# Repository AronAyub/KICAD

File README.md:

# KICAD
- **Some Old designs, this is where i began ! **
- kicad design projects
  
In this repository I have provided my previous KICAD PCB Designs for:
### Arduino hat
- this is a complete arduino hat, check the folder for files! it is among my first designs 

### Breadboard - Power Supply
- most devs use breadborad for their prototyping, learn how to create a breadboard power supply. it is among my first designs 

### Flamingo Control Board
- this was a client project, he allowed to have it open source. He is from Florida! funny enough he wanted a Flamingo shapped PCB, it is among my first designs 

### 12V 1A input to 3v3 /5V circuit 

- this is a simple power supply unit which accepts 12V, 1A and gives, 3V3 and 5V as output, it is among my first designs 

### LED Matrix Project
 - An LED Matrix based PCB using registers, this was implimented practically locally in Kenya.

### Raspberry pi Hat project

- mini Pi Hat, one of my old PCB design projects !

### Rf 2.45ghz support circuit
- the circuit schematic is in the folder 

### STRF-Kicad master
- the circuit schematic is in the folder
### 3-phase circuit
- the circuit schematic is in the folder
### Transmitter Circuit 
- the circuit schematic is in the folder

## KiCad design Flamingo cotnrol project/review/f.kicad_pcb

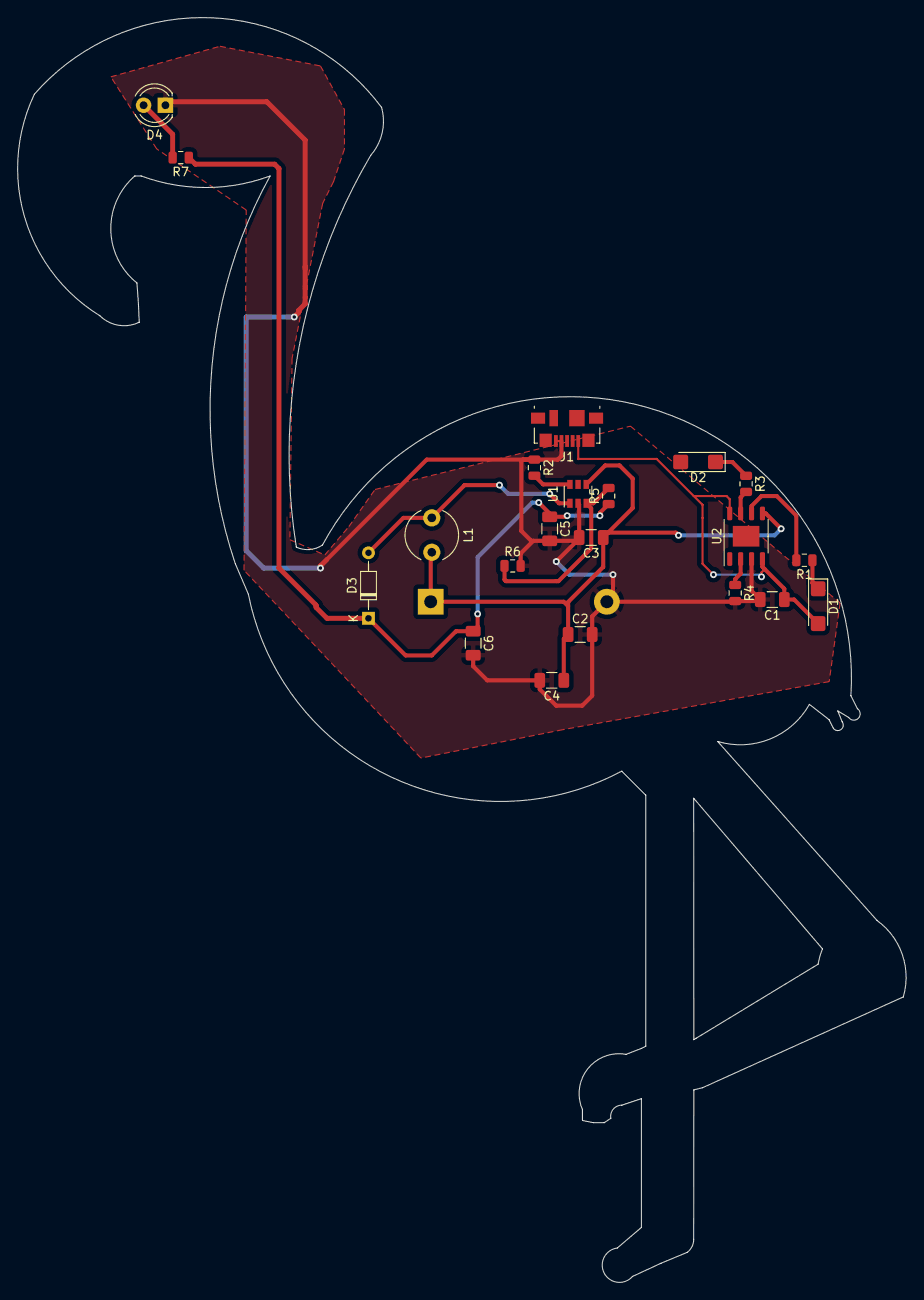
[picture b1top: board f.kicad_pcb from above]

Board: 2 copper layers, 103.4 x 147.1 mm, 22 parts (1 on the bottom side), 13 nets.

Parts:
BT1: Battery; BatteryHolder_Keystone_104_1x23mm
C1, C4: 10nF; C_1206_3216Metric
C2, C5: 20uF; C_1206_3216Metric
C3, C6: 0.1uF; C_1206_3216Metric
D1: GREEN; LED_1806_4516Metric_Castellated
D2: RED; LED_1806_4516Metric_Castellated
D3: 5.1; D_DO-34_SOD68_P7.62mm_Horizontal
D4: LED; LED_D4.0mm
J1: USB_A; USB_Micro-B_Molex_47346-0001
L1: 4.7uH; L_Radial_D6.0mm_P4.00mm
R1, R3, R7: 1k; R_0805_2012Metric
R2: 48k; R_0805_2012Metric
R4: 1.2k; R_0805_2012Metric
R5: 88k; R_0805_2012Metric
R6: 12k; R_0805_2012Metric
U1: FP6291; SOT-23-6
U2: TP4056_BT; HSOP-8-1EP_3.9x4.9mm_P1.27mm_EP2.41x3.1mm

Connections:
5OT: C5.1, C6.1, D3.1 (K), R5.1, R7.1
BAT-: BT1.2 (-), C1.2, C2.2, C3.2, C4.2, C5.2, C6.2, D4.1 (K), J1.4 (GND), J1.5 (Shield), R2.1, R4.2, R6.2, U1.2 (GND), U2.3 (GND_)
BOOST: BT1.1 (+), C2.1, C3.1, C4.1, L1.2, U1.4 (EN), U1.5 (VCC), U2.5 (BAT)
FB: R5.2, R6.1, U1.3 (FB)
unnamed: C1.1, D1.2 (A), D2.2 (A), J1.1 (VBUS), U2.4 (VCC), U2.8 (CE)
unnamed: D1.1 (K), R1.1
unnamed: D2.1 (K), R3.1
unnamed: D3.2 (A), L1.1, U1.1 (LX)
unnamed: D4.2 (A), R7.2
unnamed: R1.2, U2.6 (STDBY)
unnamed: R2.2, U1.6 (OC)
unnamed: R3.2, U2.7 (CHRG)
unnamed: R4.1, U2.2 (PROG)

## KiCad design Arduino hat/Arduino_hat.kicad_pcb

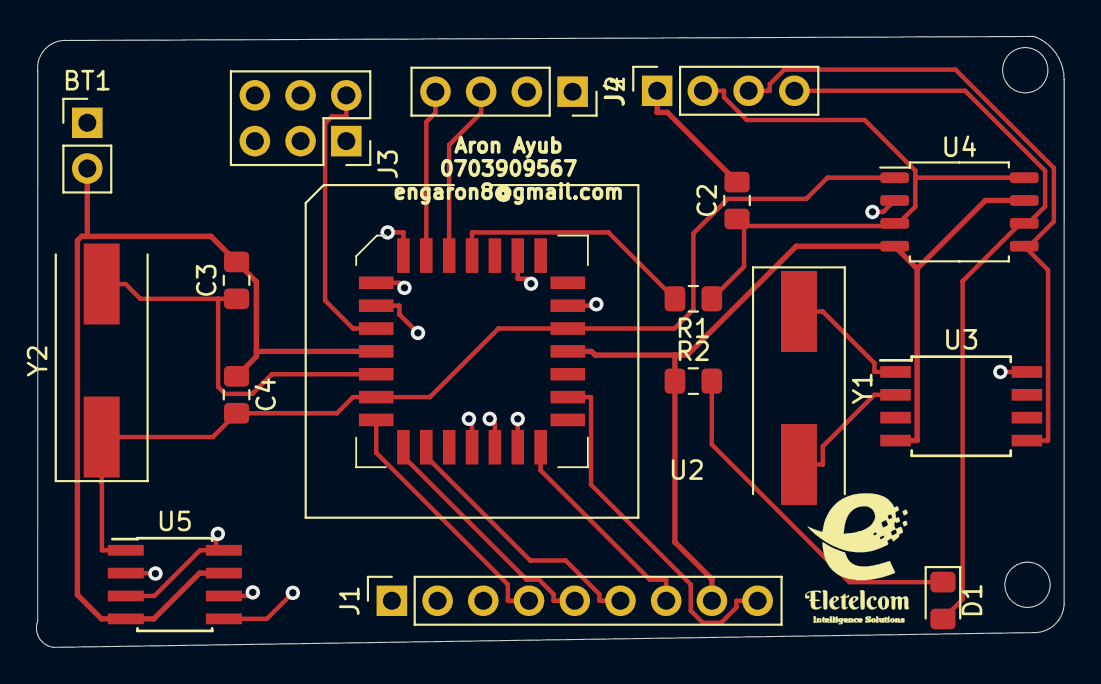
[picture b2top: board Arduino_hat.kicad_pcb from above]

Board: 4 copper layers, 57.1 x 33.9 mm, 17 parts (0 on the bottom side), 22 nets.

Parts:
BT1: 3V; PinHeader_1x02_P2.54mm_Vertical
C2: 10uF; C_0805_2012Metric_Pad1.15x1.40mm_HandSolder
C3, C4: 22pF; C_0805_2012Metric_Pad1.15x1.40mm_HandSolder
D1: LED; LED_0805_2012Metric_Pad1.15x1.40mm_HandSolder
J1: digital pins; PinSocket_1x09_P2.54mm_Vertical
J2: I2C; PinSocket_1x04_P2.54mm_Vertical
J3: ICSP; PinSocket_2x03_P2.54mm_Vertical
J4: serial; PinSocket_1x04_P2.54mm_Vertical
R1: 10Kohm; R_0805_2012Metric_Pad1.15x1.40mm_HandSolder
R2: 330ohm; R_0805_2012Metric_Pad1.15x1.40mm_HandSolder
U2: ATmega328P-PU; PLCC-28_SMD-Socket
U3: DS1337_PDv2; SOIJ-8_5.3x5.3mm_P1.27mm
U4: 24LC1025; SOIC-8_5.275x5.275mm_P1.27mm
U5: 24LC1025; PowerIntegrations_SO-8
Y1: Crystal 32MHz; Crystal_SMD_HC49-SD
Y2: Crystal 16Mhz; Crystal_SMD_HC49-SD

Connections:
/ADDR1: C4.2, U2.10, U2.23, U4.1, U5.1, Y2.1
/ADDR2: U2.24, U4.2, U5.2
/D2: J1.1, U2.4
/D3: J1.2, U2.5
/D4: J1.3, U2.6
/D5: J1.4, U2.11
/D6: J1.5, U2.12
/D7: J1.6, U2.13
/D8: J1.7, U2.18
/MISO: J3.1, U2.16
/MOSI: J3.4, U2.15
/RESET: R1.2, U2.1
/RX: J4.3, U2.2
/SCK: D1.2, J2.4, J3.3, U2.17, U4.6, U5.6
/SDA: J2.3, U2.27, U3.5, U4.5, U5.5
/TX: J4.4, U2.3
/VCC: BT1.1, C2.1, J1.9, J2.2, J3.2, J4.2, R1.1, U2.7, U2.20, U3.8, U4.3, U4.8, U5.3, U5.8
GNDPWR: BT1.2, C2.2, C3.2, C4.1, J1.8, J2.1, J3.6, J4.1, R2.1, U2.8, U2.22, U3.4, U4.4, U4.7, U5.4, U5.7
unnamed: C3.1, U2.9, Y2.2
unnamed: D1.1, R2.2
unnamed: U3.1, Y1.1
unnamed: U3.2, Y1.2

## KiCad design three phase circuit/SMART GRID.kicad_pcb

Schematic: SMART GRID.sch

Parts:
1Mohm1, 1Mohm2, 1Mohm3, 1Mohm4, 1Mohm5: 47k; R_Axial_DIN0309_L9.0mm_D3.2mm_P12.70mm_Horizontal
C1, C2, C6, C7, C8, C9: 2A103J; C_Disc_D9.0mm_W5.0mm_P5.00mm
C3, C10, C11: 10uF 16v; CP_Radial_D4.0mm_P1.50mm
C4, C12, C13: 47uf; CP_Radial_D4.0mm_P1.50mm
C5: 2A104J; C_Disc_D9.0mm_W5.0mm_P5.00mm
C14, C15: 2A104J; C_Disc_D11.0mm_W5.0mm_P5.00mm
C16: 2A123J; C_Disc_D11.0mm_W5.0mm_P5.00mm
C17: 2A123J; C_Disc_D11.0mm_W5.0mm_P7.50mm
C18: 2A104J; C_Disc_D11.0mm_W5.0mm_P7.50mm
D1: 1N4007-T_NRND; DO-41; MPN 1N4007-T; Digi-Key_PN 1N4007DICT-ND
D2, D3, D4, D5, D6, D7, D8, D9, D10, D11, D12: 1N4007-T_NRND; D_5W_P12.70mm_Horizontal; MPN 1N4007-T; Digi-Key_PN 1N4007DICT-ND
J1: Screw_Terminal_01x04; TerminalBlock_Altech_AK300-4_P5.00mm
R1: 1M; R_Axial_DIN0309_L9.0mm_D3.2mm_P12.70mm_Horizontal
R2, R7, R11: 100K; R_Axial_DIN0309_L9.0mm_D3.2mm_P15.24mm_Horizontal
R3, R5, R8, R12, R14, R15: 10K; R_Axial_DIN0309_L9.0mm_D3.2mm_P15.24mm_Horizontal
R4, R9, R13: 2.2K; R_Axial_DIN0309_L9.0mm_D3.2mm_P15.24mm_Horizontal
R6, R10: 1M; R_Axial_DIN0309_L9.0mm_D3.2mm_P15.24mm_Horizontal
R16: 47k; R_Axial_DIN0309_L9.0mm_D3.2mm_P15.24mm_Horizontal
U1, U2, U3: LM3578; DIP-8_W7.62mm

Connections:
/A0: R16.1, U1.1
/A1: 1Mohm1.1, U2.1
/A2: 1Mohm3.1, U3.1
/GND: 1Mohm2.2, 1Mohm4.2, 1Mohm5.2, C1.2, C2.2, C3.2, C4.2, C5.1, C6.2, C7.2, C8.2, C9.2, C10.2, C11.2, C12.2, C13.2, C14.1, C15.1, C16.1, C17.1, C18.1, R4.2, R9.2, R13.2, U1.4, U2.4, U3.4; also elsewhere on the board
/L1: D1.K, J1.4
/L2: J1.3
/L3: J1.2
/N: D1.A, J1.1
/SG1: C1.1, R1.1
/SG2: C6.1, R6.1
/SG3: C7.1, R10.1
/VCC: C16.2, C17.2, C18.2, U1.8, U2.8, U3.8; also elsewhere on the board
unnamed: 1Mohm1.2, 1Mohm4.1, U2.2
unnamed: 1Mohm2.1, R16.2, U1.2
unnamed: 1Mohm3.2, 1Mohm5.1, U3.2
unnamed: C2.1, C3.1, R3.2, R4.1, R5.2
unnamed: C4.1, R5.1
unnamed: C5.2, U1.5
unnamed: C8.1, C10.1, R8.2, R9.1, R14.2
unnamed: C9.1, C11.1, R12.2, R13.1, R15.2
unnamed: C12.1, R14.1
unnamed: C13.1, R15.1
unnamed: C14.2, U2.5
unnamed: C15.2, U3.5
unnamed: R1.2, R2.1
unnamed: R2.2, R3.1
unnamed: R6.2, R7.1
unnamed: R7.2, R8.1
unnamed: R10.2, R11.1
unnamed: R11.2, R12.1
unnamed: U1.3, U1.6, U1.7
unnamed: U2.3, U2.6, U2.7
unnamed: U3.3, U3.6, U3.7

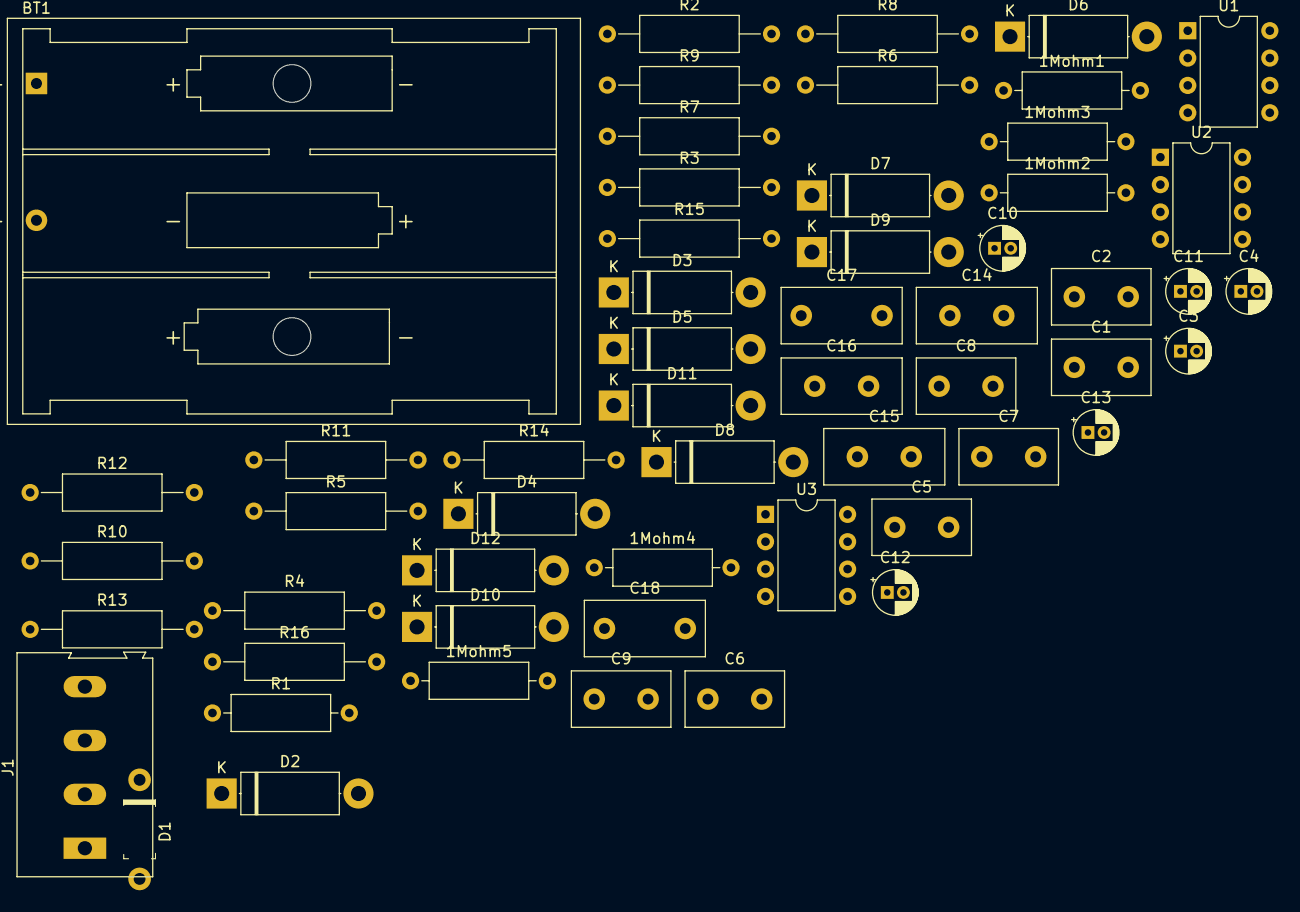
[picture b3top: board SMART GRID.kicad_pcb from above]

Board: 2 copper layers, 56 parts (0 on the bottom side), 31 nets, no tracks yet.

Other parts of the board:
BT1: 6V; BatteryHolder_Keystone_2479_3xAAA

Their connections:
/GND: BT1.2; also elsewhere on the board
/VCC: BT1.1; also elsewhere on the board

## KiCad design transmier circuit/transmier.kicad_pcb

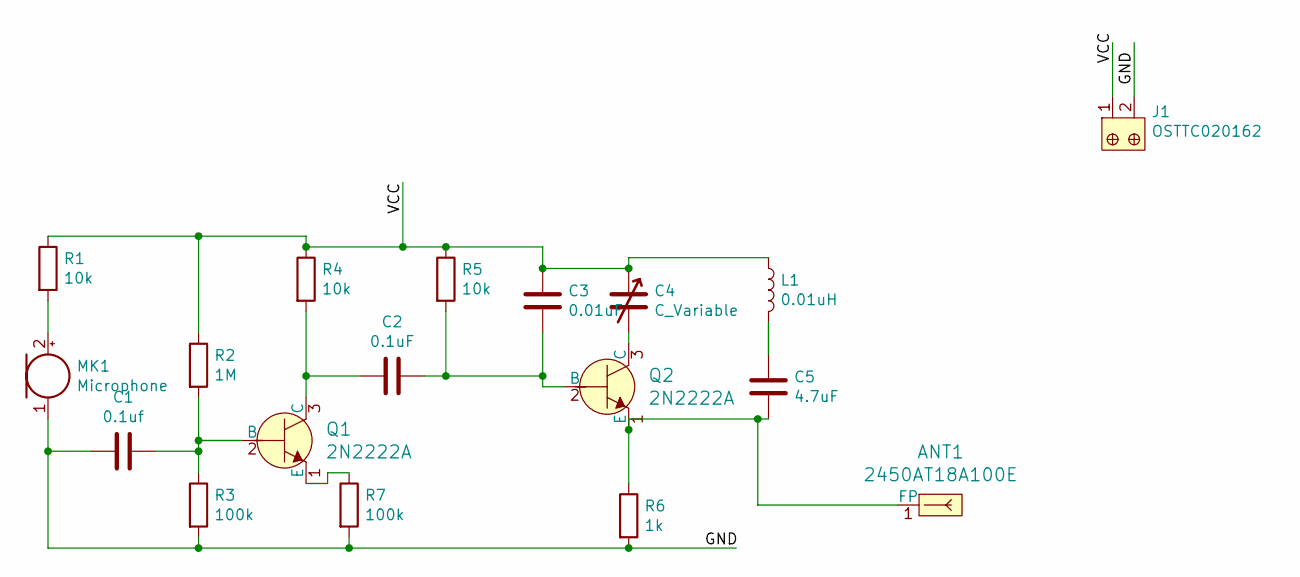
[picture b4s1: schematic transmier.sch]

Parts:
ANT1: 2450AT18A100E; Pin_D0.9mm_L10.0mm_W2.4mm_FlatFork; MPN 2450AT18A100E; Digi-Key_PN 712-1005-1-ND
C1: 0.1uf; C_Disc_D12.0mm_W4.4mm_P7.75mm
C2: 0.1uF; C_Disc_D12.0mm_W4.4mm_P7.75mm
C3: 0.01uF; C_Disc_D12.0mm_W4.4mm_P7.75mm
C4: C_Variable; C_Rect_L7.0mm_W6.5mm_P5.00mm
C5: 4.7uF; C_Disc_D7.5mm_W5.0mm_P5.00mm
J1: OSTTC020162; C_Disc_D12.0mm_W4.4mm_P7.75mm; MPN OSTTC020162; Digi-Key_PN ED2600-ND
L1: 0.01uH; L_Axial_L14.0mm_D4.5mm_P15.24mm_Horizontal_Fastron_LACC
MK1: Microphone; L_Radial_D10.5mm_P5.00mm_Abacron_AISR-01
Q1, Q2: 2N2222A; TO-18-3; MPN 2N2222A; Digi-Key_PN 2N2222ACS-ND
R1, R4, R5: 10k; R_Axial_DIN0614_L14.3mm_D5.7mm_P15.24mm_Horizontal
R2: 1M; R_Axial_DIN0614_L14.3mm_D5.7mm_P15.24mm_Horizontal
R3, R7: 100k; R_Axial_DIN0614_L14.3mm_D5.7mm_P15.24mm_Horizontal
R6: 1k; R_Axial_DIN0614_L14.3mm_D5.7mm_P15.24mm_Horizontal

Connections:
/GND: C1.2, J1.2, MK1.1 (-), R3.2, R6.2, R7.2
/VCC: C3.2, C4.1, J1.1, L1.1, R1.1, R2.1, R4.1, R5.1
unnamed: ANT1.1 (FP), C5.1, Q2.1 (E), R6.1
unnamed: C1.1, Q1.2 (B), R2.2, R3.1
unnamed: C2.1, C3.1, Q2.2 (B), R5.2
unnamed: C2.2, Q1.3 (C), R4.2
unnamed: C4.2, Q2.3 (C)
unnamed: C5.2, L1.2
unnamed: MK1.2 (+), R1.2
unnamed: Q1.1 (E), R7.1

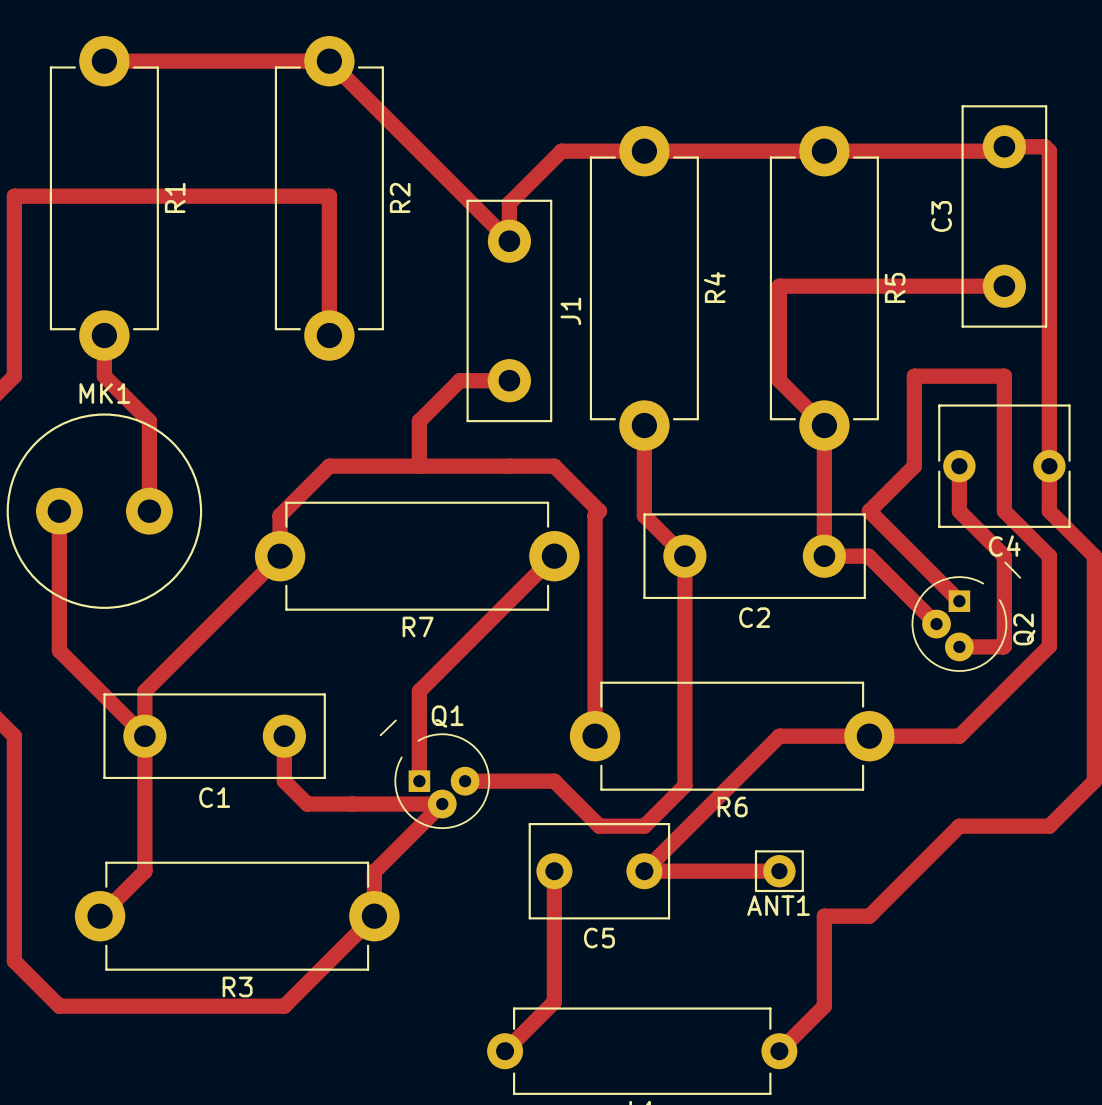
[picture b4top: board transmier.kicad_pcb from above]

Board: 2 copper layers, 18 parts (0 on the bottom side), 10 nets.

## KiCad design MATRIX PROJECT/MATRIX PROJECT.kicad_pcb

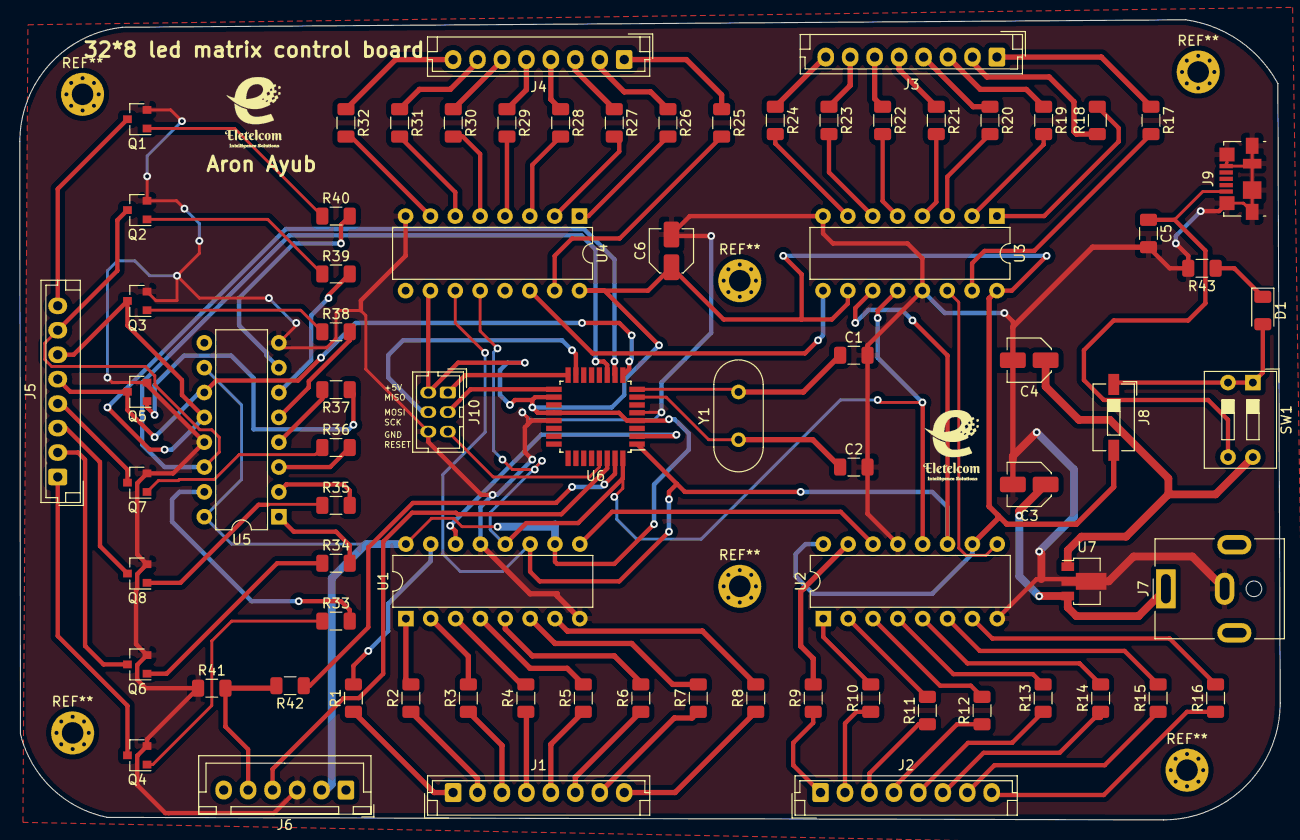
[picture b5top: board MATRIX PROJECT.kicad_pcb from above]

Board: 2 copper layers, 128.8 x 81.8 mm, 77 parts (0 on the bottom side), 110 nets.

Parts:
C1, C2: 22pf; C_1206_3216Metric
C3, C6: 10uf; C_Elec_4x5.4
C4: 1uf; C_Elec_4x5.4
C5: 10uf; C_1206_3216Metric
D1: LED; LED_1206_3216Metric
J1: SRA; JST_EH_B8B-EH-A_1x08_P2.50mm_Vertical
J2: SRB; JST_EH_B8B-EH-A_1x08_P2.50mm_Vertical
J3: SRC; JST_EH_B8B-EH-A_1x08_P2.50mm_Vertical
J4: SRD; JST_EH_B8B-EH-A_1x08_P2.50mm_Vertical
J5: ROW SW; JST_EH_B8B-EH-A_1x08_P2.50mm_Vertical
J6: BT SENSOR; JST_XH_B6B-XH-A_1x06_P2.50mm_Vertical
J7: Barrel_Jack_Switch; BarrelJack_CUI_PJ-063AH_Horizontal
J8: PWON; SW_DIP_SPSTx01_Slide_6.7x4.1mm_W6.73mm_P2.54mm_LowProfile_J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
J9: USB_B_Micro; USB_Micro-B_Molex_47346-0001
J10: ICSP; Hirose_DF11-6DP-2DSA_2x03_P2.00mm_Vertical
Q1, Q2, Q3, Q4, Q5, Q6, Q7, Q8: BJT; SOT-23
R1, R2, R3, R4, R5, R6, R7, R8, R9, R10, R11, R12, R13, R14, R15, R16, R17, R18, R19, R20, R21, R22, R23, R24, R25, R26, R27, R28, R29, R30, R31, R32: 220ohm; R_1206_3216Metric
R33, R34, R35, R36, R37, R38, R39, R40: 1k; R_1206_3216Metric
R41: 2K; R_1206_3216Metric
R42, R43: 1K; R_1206_3216Metric
SW1: SW_DIP_x02; SW_DIP_SPSTx02_Slide_9.78x7.26mm_W7.62mm_P2.54mm
U1, U2, U3, U4, U5: 74HC595; DIP-16_W7.62mm
U6: ATmega328PB-AU; TQFP-32_7x7mm_P0.8mm
U7: L78L05_SOT89; SOT-89-3
Y1: Crystal; Crystal_HC49-4H_Vertical

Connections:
+5V: C6.1, J6.2, J8.2, J10.2, U1.10, U1.16, U2.10, U2.16, U3.10, U3.16, U4.10, U4.16, U5.10, U5.16, U6.4, U6.18, U6.20
/12_5_S: C4.1, SW1.4, U7.1
/MISO: J10.1, U6.16
/MOSI: J10.4, U6.15
/P1: J5.1, Q4.3
/P2: J5.2, Q6.3
/P3: J5.3, Q8.3
/P4: J5.4, Q7.3
/P5: J5.5, Q5.3, U5.11, U6.9
/P6: J5.6, Q3.3, U5.12, U6.10
/P7: J5.7, Q2.3, U5.14, U6.11
/P8: J5.8, Q1.3
/PIN2: U1.11, U2.11, U3.11, U4.11, U6.1
/PIN3: U1.12, U2.12, U3.12, U4.12, U6.32
/PIN4: U1.14, U6.2
/PW: D1.2, J8.1, SW1.1, SW1.2
/QA: Q4.1, R33.1
/QB: Q6.1, R34.1
/QC: Q8.1, R35.1
/QD: Q7.1, R36.1
/QE: Q5.1, R37.1
/QF: Q3.1, R38.1
/QG: Q2.1, R39.1
/QH: Q1.1, R40.1
/QH2: U2.9, U3.14
/RESET: J10.5, U6.29
/RX: J6.4, U6.30
/SCK: J10.3, U6.17
/TX: R42.1, U6.31
/USB_S: C5.1, J9.1, SW1.3
/VIN: C3.1, J7.1, U7.3
GND: C1.2, C2.2, C3.2, C4.2, C5.2, C6.2, J6.3, J7.2, J9.5, J9.6, J10.6, Q1.2, Q2.2, Q3.2, Q4.2, Q5.2, Q6.2, Q7.2, Q8.2, R41.1, R43.2, U1.8, U1.13, U2.8, U2.13, U3.8, U3.13, U4.8, U5.8, U5.13, U6.5, U6.21, U7.2
unnamed: C1.1, U6.8, Y1.2
unnamed: C2.1, U6.7, Y1.1
unnamed: D1.1, R43.1
unnamed: J1.1, R1.1
unnamed: J1.2, R2.1
unnamed: J1.3, R3.1
unnamed: J1.4, R4.1
unnamed: J1.5, R5.1
unnamed: J1.6, R6.1
unnamed: J1.7, R7.1
unnamed: J1.8, R8.1
unnamed: J2.1, R9.1
unnamed: J2.2, R10.1
unnamed: J2.3, R11.1
unnamed: J2.4, R12.1
unnamed: J2.5, R13.1
unnamed: J2.6, R14.1
unnamed: J2.7, R15.1
unnamed: J2.8, R16.1
unnamed: J3.1, R17.1
unnamed: J3.2, R18.1
unnamed: J3.3, R19.1
unnamed: J3.4, R20.1
unnamed: J3.5, R21.1
unnamed: J3.6, R22.1
unnamed: J3.7, R23.1
unnamed: J3.8, R24.1
unnamed: J4.1, R25.1
unnamed: J4.2, R26.1
unnamed: J4.3, R27.1
unnamed: J4.4, R28.1
unnamed: J4.5, R29.1
unnamed: J4.6, R30.1
unnamed: J4.7, R31.1
unnamed: J4.8, R32.1
unnamed: J6.5, R41.2, R42.2
unnamed: R1.2, U1.15
unnamed: R2.2, U1.1
unnamed: R3.2, U1.2
unnamed: R4.2, U1.3
unnamed: R5.2, U1.4
unnamed: R6.2, U1.5
unnamed: R7.2, U1.6
unnamed: R8.2, U1.7
unnamed: R9.2, U2.15
unnamed: R10.2, U2.1
unnamed: R11.2, U2.2
unnamed: R12.2, U2.3
unnamed: R13.2, U2.4
unnamed: R14.2, U2.5
unnamed: R15.2, U2.6
unnamed: R16.2, U2.7
unnamed: R17.2, U3.15
unnamed: R18.2, U3.1
unnamed: R19.2, U3.2
unnamed: R20.2, U3.3
unnamed: R21.2, U3.4
unnamed: R22.2, U3.5
unnamed: R23.2, U3.6
unnamed: R24.2, U3.7
unnamed: R25.2, U4.15
unnamed: R26.2, U4.1
unnamed: R27.2, U4.2
unnamed: R28.2, U4.3
unnamed: R29.2, U4.4
unnamed: R30.2, U4.5
unnamed: R31.2, U4.6
unnamed: R32.2, U4.7
unnamed: R33.2, U5.15
unnamed: R34.2, U5.1
unnamed: R35.2, U5.2
unnamed: R36.2, U5.3
unnamed: R37.2, U5.4
unnamed: R38.2, U5.5
unnamed: R39.2, U5.6
unnamed: R40.2, U5.7
unnamed: U1.9, U2.14
unnamed: U3.9, U4.14

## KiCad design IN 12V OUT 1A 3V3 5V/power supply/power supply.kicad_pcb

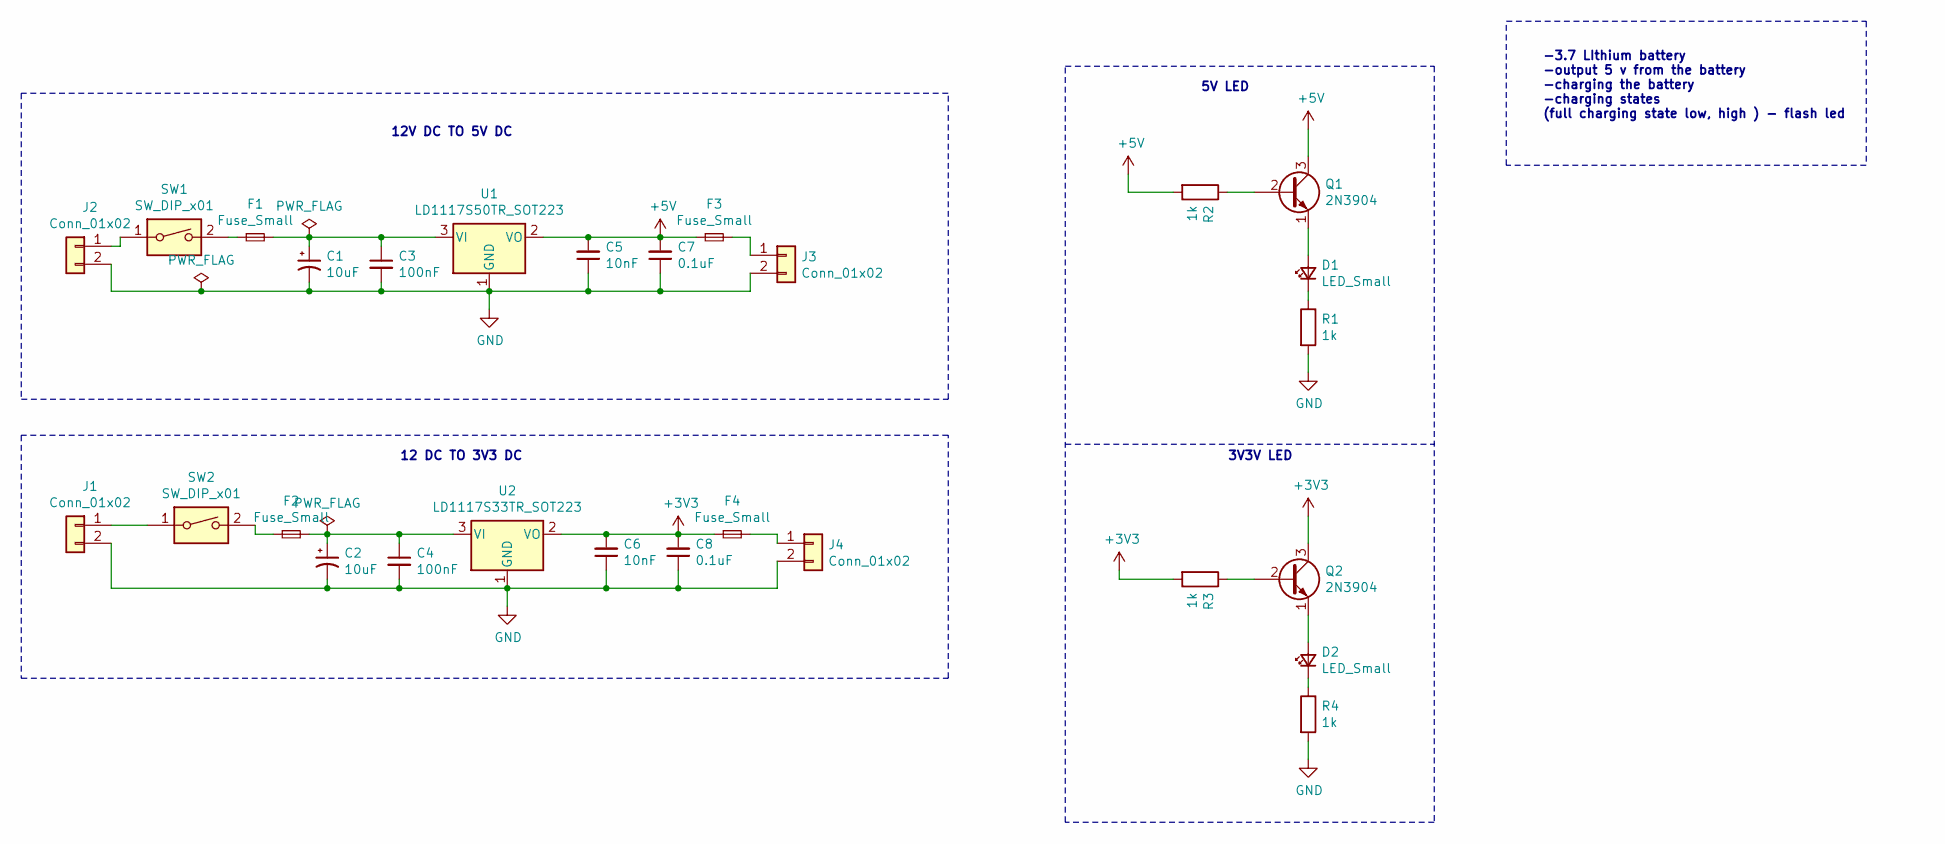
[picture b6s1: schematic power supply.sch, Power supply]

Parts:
C1, C2: 10uF; C_1206_3216Metric
C3, C4: 100nF; C_1206_3216Metric
C5, C6: 10nF; C_1206_3216Metric
C7, C8: 0.1uF; C_1206_3216Metric
D1, D2: LED_Small; LED_D5.0mm
F1, F2, F3, F4: Fuse_Small; Fuseholder_TR5_Littelfuse_No560_No460
J1, J2, J3, J4: Conn_01x02; Altech_AK300_1x02_P5.00mm_45-Degree
Q1, Q2: 2N3904; TO-92_Inline
R1, R2, R3, R4: 1k; R_1206_3216Metric
SW1, SW2: SW_DIP_x01; SW_DIP_SPSTx01_Piano_10.8x4.1mm_W7.62mm_P2.54mm
U1: LD1117S50TR_SOT223; SOT-223-3_TabPin2
U2: LD1117S33TR_SOT223; SOT-223-3_TabPin2

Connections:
+3V3: C6.2, C8.2, F4.1, Q2.3 (C), R3.2, U2.2 (VO)
+5V: C5.2, C7.2, F3.1, Q1.3 (C), R2.2, U1.2 (VO)
GND: C1.2, C2.2, C3.2, C4.2, C5.1, C6.1, C7.1, C8.1, J1.2, J2.2, J3.2, J4.2, R1.2, R4.2, U1.1 (GND), U2.1 (GND)
unnamed: C1.1, C3.1, F1.2, U1.3 (VI)
unnamed: C2.1, C4.1, F2.2, U2.3 (VI)
unnamed: D1.1 (K), R1.1
unnamed: D1.2 (A), Q1.1 (E)
unnamed: D2.1 (K), R4.1
unnamed: D2.2 (A), Q2.1 (E)
unnamed: F1.1, SW1.2
unnamed: F2.1, SW2.2
unnamed: F3.2, J3.1
unnamed: F4.2, J4.1
unnamed: J1.1, SW2.1
unnamed: J2.1, SW1.1
unnamed: Q1.2 (B), R2.1
unnamed: Q2.2 (B), R3.1

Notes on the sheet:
5V LED
3V3V LED
12V DC TO 5V DC
12 DC TO 3V3 DC
-3.7 LIthium battery -output 5 v from the battery -charging the battery -charging states (full charging state low, high ) - flash led

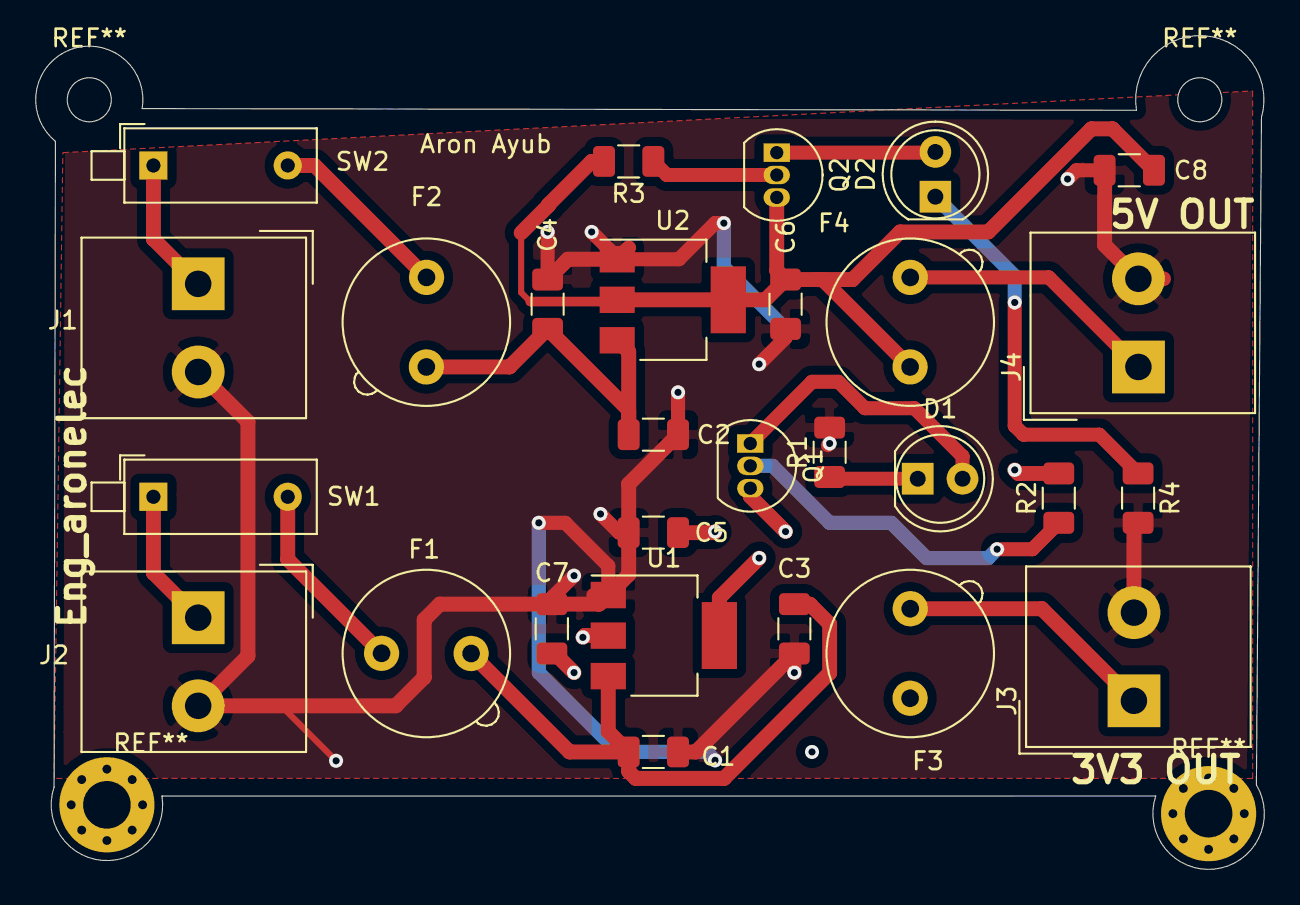
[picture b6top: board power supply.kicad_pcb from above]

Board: 4 copper layers, 69.7 x 47.3 mm, 28 parts (0 on the bottom side), 17 nets.

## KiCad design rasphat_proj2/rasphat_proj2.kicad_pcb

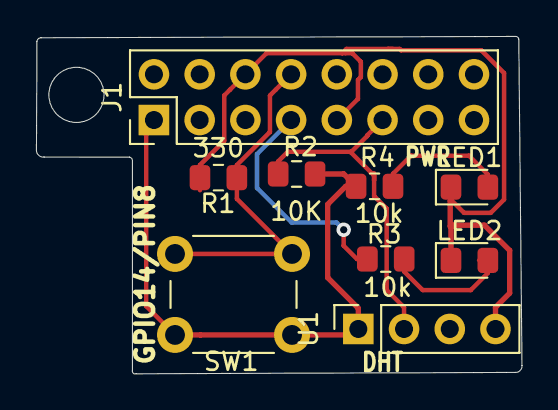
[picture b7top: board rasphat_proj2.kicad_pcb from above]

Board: 2 copper layers, 27.0 x 18.7 mm, 9 parts (0 on the bottom side), 7 nets.

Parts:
J1: Raspberry_Pi_2_3; PinHeader_2x08_P2.54mm_Vertical
LED1, LED2: LED; LED_0805_2012Metric_Pad1.15x1.40mm_HandSolder
R1: 330; R_0805_2012Metric_Pad1.15x1.40mm_HandSolder
R2: 10K; R_0805_2012Metric_Pad1.15x1.40mm_HandSolder
R3, R4: 10k; R_0805_2012Metric_Pad1.15x1.40mm_HandSolder
SW1: SW_DPST; SW_PUSH_6mm_H8mm
U1: DHT22; PinSocket_1x04_P2.54mm_Vertical

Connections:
/3V3: J1.1, R2.2, R4.2, SW1.1, U1.1
/button_input: J1.8, R1.1, SW1.2
GND: J1.6, J1.9, LED1.1, LED2.1, R1.2, U1.4
unnamed: LED2.2, R3.1
unnamed: LED1.2, R4.1
unnamed: J1.7, R3.2
unnamed: J1.11, R2.1, U1.2

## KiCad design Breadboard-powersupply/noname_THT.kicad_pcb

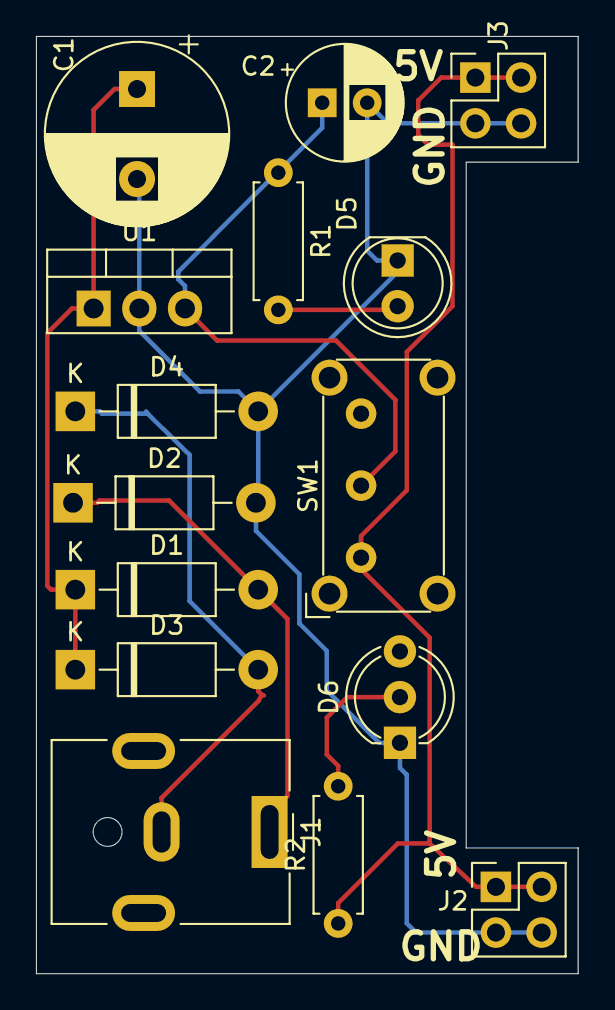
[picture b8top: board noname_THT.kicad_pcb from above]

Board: 2 copper layers, 30.1 x 52.1 mm, 15 parts (0 on the bottom side), 8 nets.

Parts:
C1: 47uF; CP_Radial_D10.0mm_P5.00mm
C2: 470uF; CP_Radial_D6.3mm_P2.50mm
D1, D2, D3, D4: 1N4007; D_DO-41_SOD81_P10.16mm_Horizontal
D5: LED; LED_D5.0mm
D6: LED; LED_D5.0mm-3
J1: Barrel_Jack_Switch; BarrelJack_CUI_PJ-063AH_Horizontal
J2, J3: Conn_02x02_Counter_Clockwise; PinHeader_2x02_P2.54mm_Vertical
R1, R2: 560; R_Axial_DIN0207_L6.3mm_D2.5mm_P7.62mm_Horizontal
SW1: SW_DPDT_x2; SW_E-Switch_EG1224_SPDT_Angled
U1: LM7805_TO220; TO-220-3_Vertical

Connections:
/V-: C1.2, C2.2, D2.2, D4.2, D5.1, D6.1, J2.3, J2.4, J3.3, J3.4, U1.2
/Vin: C1.1, D1.1, D3.1, U1.1
/Vout1: C2.1, R1.1, SW1.2, U1.3
unnamed: D1.2, D2.1, J1.1
unnamed: D3.2, D4.1, J1.2
unnamed: D5.2, R1.2
unnamed: D6.2, R2.2
unnamed: J2.1, J2.2, J3.1, J3.2, R2.1, SW1.1

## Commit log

2021-05-03 KICAD Design
    >this repository contains some few designs i did.
    >there are schematics
    >PCB 3D views
    >Garber files for the designs
    >THT and SMD provided
2021-05-03 Arduino_hat design
2021-07-08 smart power supply
    input 12 v dc
    output
    3.3v
    5v
2021-07-08 st rf clone project
    this helps in signal harvesting
2021-09-12 matrix project
    high density matrix LED control Board
2021-09-12 flamingo control project
    project for a USA guy
2023-01-25 update photos
